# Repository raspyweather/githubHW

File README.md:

#  Github Calendar in Hardware
This is a very basic try to bring github's calendar to hardware. Who wouldn't like to get up and look at the glorious contribution history of the path?

(not my calendar btw ☺)

# introduction
Since I'm a student, manufacturing cost need to be low, why I decided to use three 10cm x 10cm pcbs and solder all components by hand. Because it is cheaper using one mutli-purpose board than two specific pcb designs, I decided to do so, not assemblying unnecessary components on these boards. 

## first/main pcb
All parts assembled 
- WeMos D1 mini (KiCad files used from https://github.com/jerome-labidurie/d1_mini_kicad)
- 2x [TPIC6B595N](http://www.ti.com/lit/ds/symlink/tpic6b595.pdf)
- [TLC5940](http://www.ti.com/lit/ds/symlink/tlc5940.pdf)
- *some* leds
- 4x Buttons
- 1x Poti

## following two pcbs
- TLC5940
- *some* leds

## Total Circuit (connected ones)
only TLC5940 and leds assembled.

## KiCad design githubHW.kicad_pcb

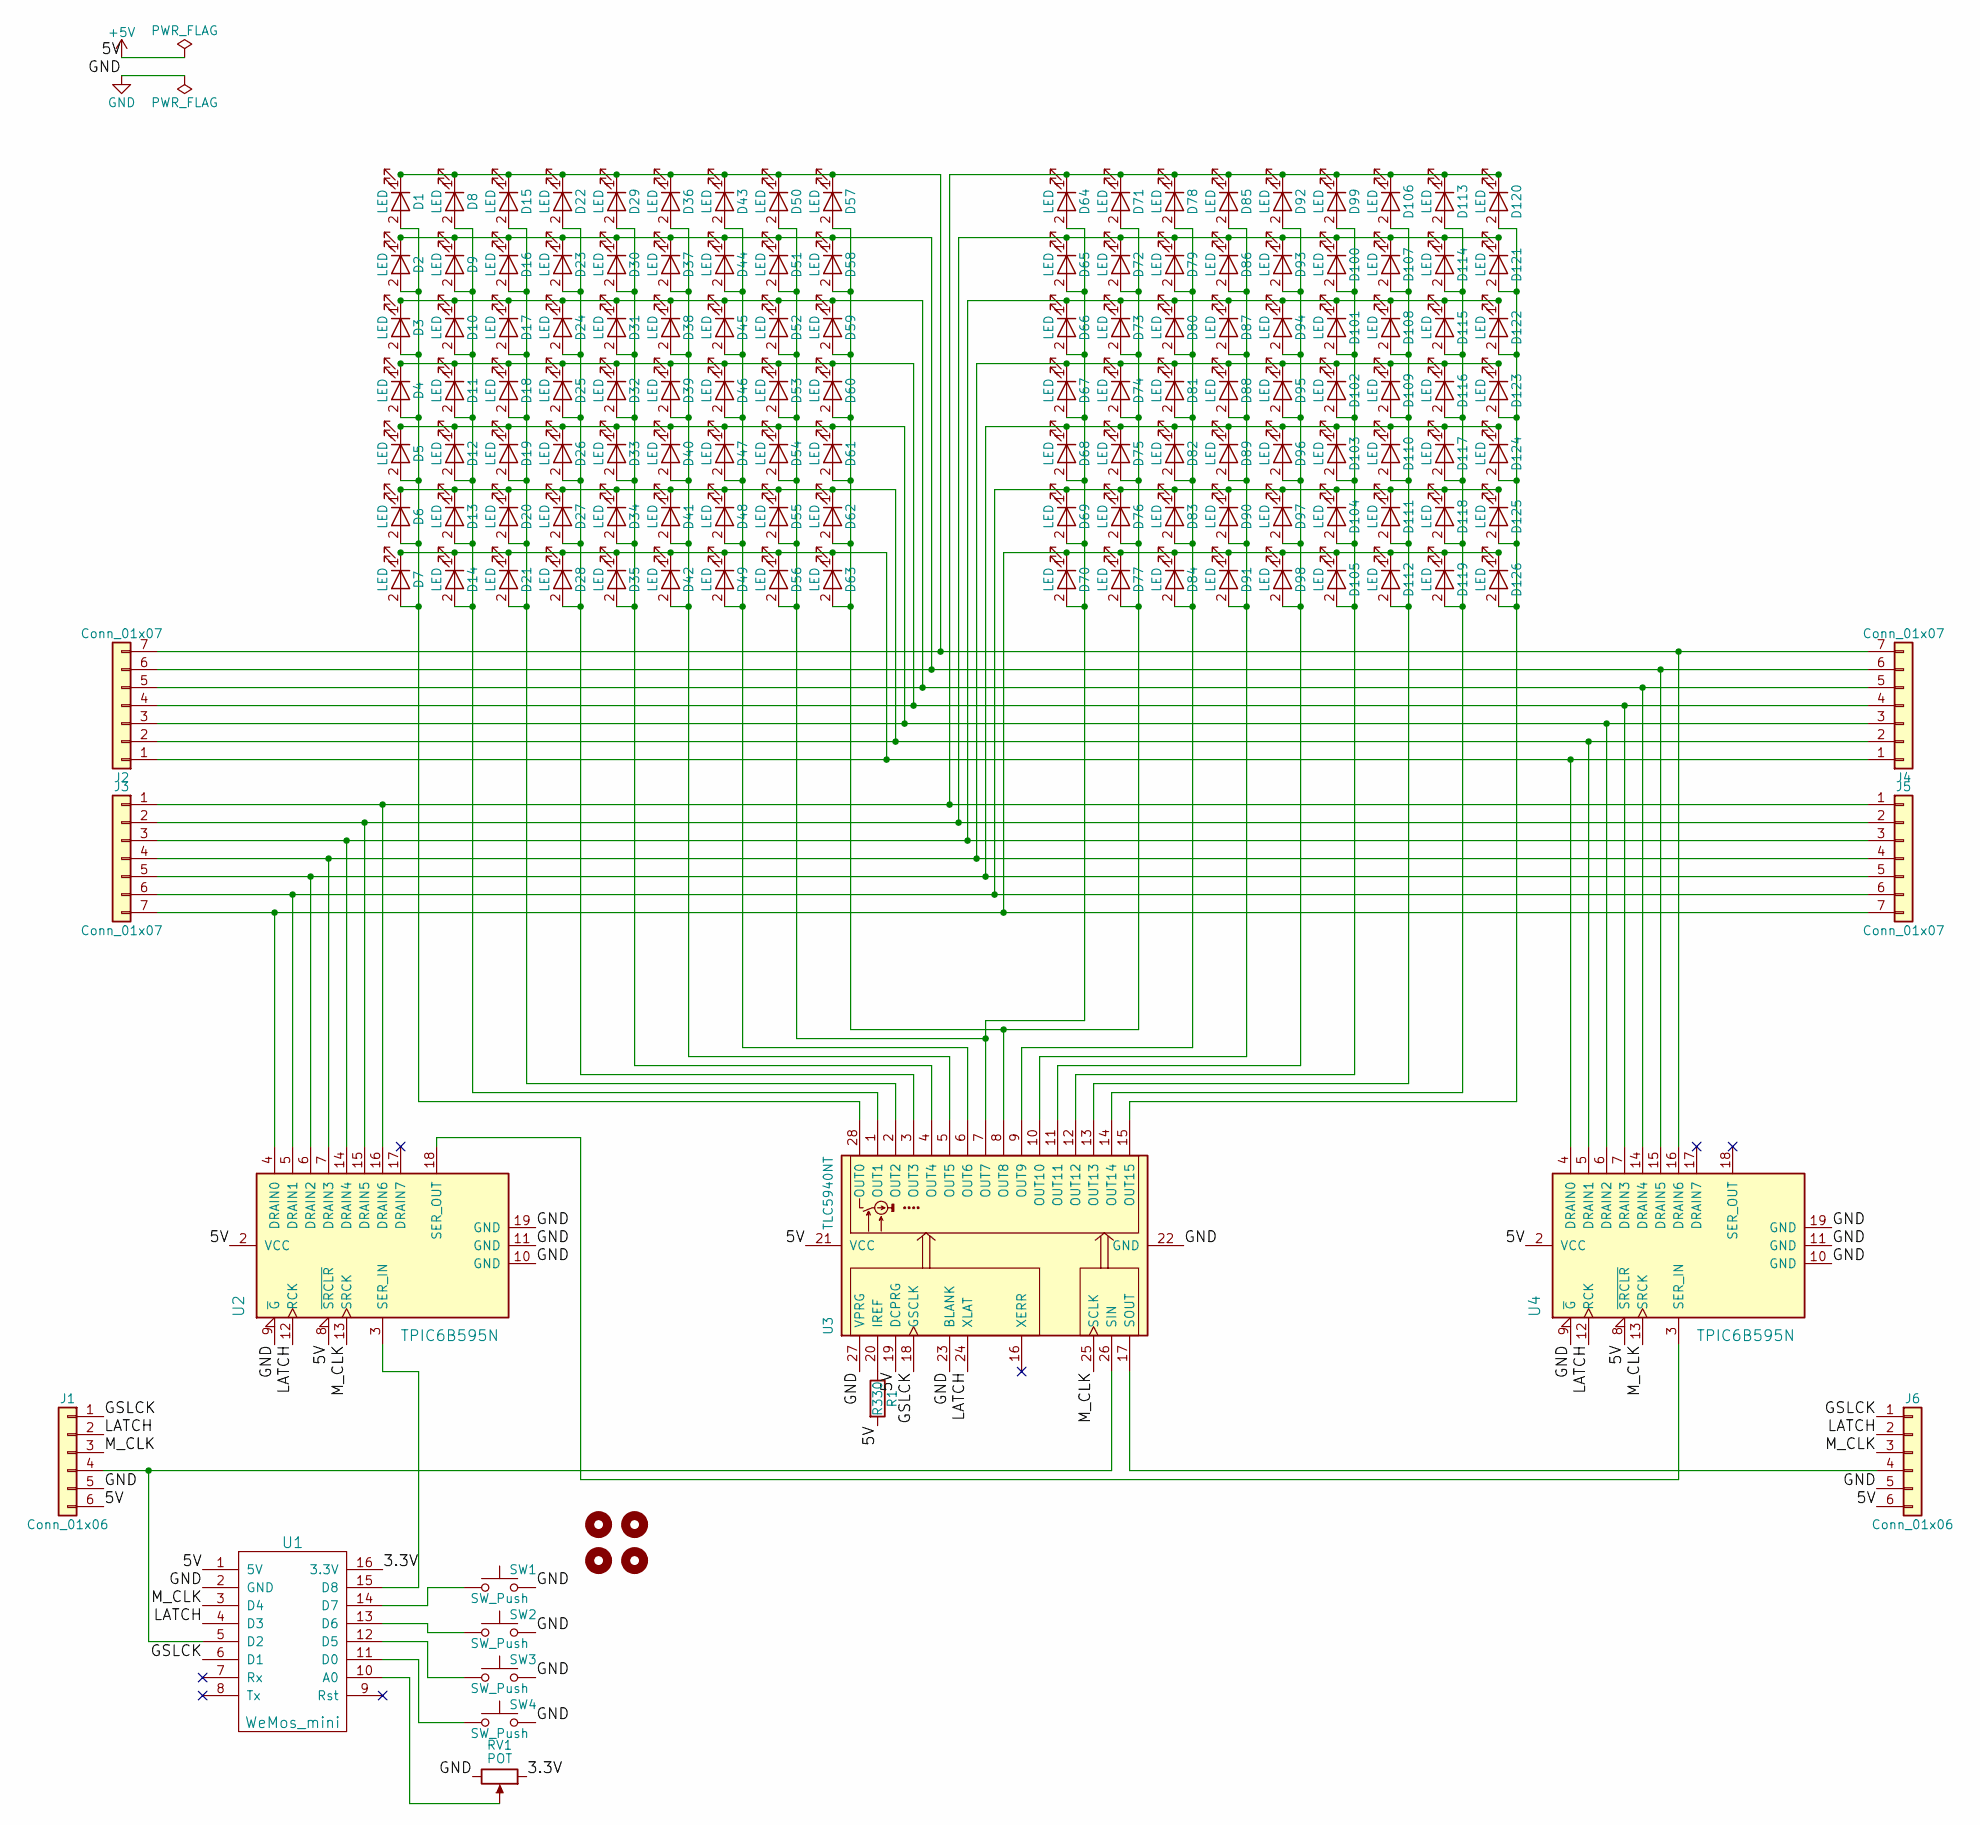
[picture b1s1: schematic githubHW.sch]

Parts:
D1, D2, D3, D4, D5, D6, D7, D8, D9, D10, D11, D12, D13, D14, D15, D16, D17, D18, D19, D20, D21, D22, D23, D24, D25, D26, D27, D28, D29, D30, D31, D32, D33, D34, D35, D36, D37, D38, D39, D40, D41, D42, D43, D44, D45, D46, D47, D48, D49, D50, D51, D52, D53, D54, D55, D56, D57, D58, D59, D60, D61, D62, D63, D64, D65, D66, D67, D68, D69, D70, D71, D72, D73, D74, D75, D76, D77, D78, D79, D80, D81, D82, D83, D84, D85, D86, D87, D88, D89, D90, D91, D92, D93, D94, D95, D96, D97, D98, D99, D100, D101, D102, D103, D104, D105, D106, D107, D108, D109, D110, D111, D112, D113, D114, D115, D116, D117, D118, D119, D120, D121, D122, D123, D124, D125, D126: LED; LED_D3.0mm
J1, J6: Conn_01x06; Pin_Header_Straight_1x06_Pitch2.00mm
J2, J3, J4, J5: Conn_01x07; Pin_Header_Straight_1x07_Pitch2.00mm
MH1, MH2, MH3, MH4: MOUNTHOLE; MountingHole_3.2mm_M3_ISO14580_Pad
R1: R330; R_Axial_DIN0204_L3.6mm_D1.6mm_P7.62mm_Horizontal
RV1: POT; Potentiometer_WirePads_largePads
SW1, SW2, SW3, SW4: SW_Push; SW_PUSH_6mm
U1: WeMos_mini; D1_mini_board
U2, U4: TPIC6B595N; DIP-20_W7.62mm
U3: TLC5940NT; DIP-28_W7.62mm

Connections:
+5V: J1.6, J6.6, R1.2, U1.1 (5V), U2.2 (VCC), U2.8 (~SRCLR), U3.19 (DCPRG), U3.21 (VCC), U4.2 (VCC), U4.8 (~SRCLR)
/3.3V: RV1.1, U1.16 (3.3V)
/GSLCK: J1.1, J6.1, U1.6 (D1), U3.18 (GSCLK)
/LATCH: J1.2, J6.2, U1.4 (D3), U2.12 (RCK), U3.24 (XLAT), U4.12 (RCK)
/M_CLK: J1.3, J6.3, U1.3 (D4), U2.13 (SRCK), U3.25 (SCLK), U4.13 (SRCK)
GND: J1.5, J6.5, RV1.3, SW1.2, SW2.2, SW3.2, SW4.2, U1.2 (GND), U2.9 (~G), U2.10 (GND), U2.11 (GND), U2.19 (GND), U3.22 (GND), U3.23 (BLANK), U3.27 (VPRG), U4.9 (~G), U4.10 (GND), U4.11 (GND), U4.19 (GND)
unnamed: D1.1 (K), D8.1 (K), D15.1 (K), D22.1 (K), D29.1 (K), D36.1 (K), D43.1 (K), D50.1 (K), D57.1 (K), J2.7, J4.7, U4.16 (DRAIN6)
unnamed: D1.2 (A), D2.2 (A), D3.2 (A), D4.2 (A), D5.2 (A), D6.2 (A), D7.2 (A), U3.28 (OUT0)
unnamed: D3.1 (K), D10.1 (K), D17.1 (K), D24.1 (K), D31.1 (K), D38.1 (K), D45.1 (K), D52.1 (K), D59.1 (K), J2.5, J4.5, U4.14 (DRAIN4)
unnamed: D8.2 (A), D9.2 (A), D10.2 (A), D11.2 (A), D12.2 (A), D13.2 (A), D14.2 (A), U3.1 (OUT1)
unnamed: D4.1 (K), D11.1 (K), D18.1 (K), D25.1 (K), D32.1 (K), D39.1 (K), D46.1 (K), D53.1 (K), D60.1 (K), J2.4, J4.4, U4.7 (DRAIN3)
unnamed: D5.1 (K), D12.1 (K), D19.1 (K), D26.1 (K), D33.1 (K), D40.1 (K), D47.1 (K), D54.1 (K), D61.1 (K), J2.3, J4.3, U4.6 (DRAIN2)
unnamed: D6.1 (K), D13.1 (K), D20.1 (K), D27.1 (K), D34.1 (K), D41.1 (K), D48.1 (K), D55.1 (K), D62.1 (K), J2.2, J4.2, U4.5 (DRAIN1)
unnamed: D7.1 (K), D14.1 (K), D21.1 (K), D28.1 (K), D35.1 (K), D42.1 (K), D49.1 (K), D56.1 (K), D63.1 (K), J2.1, J4.1, U4.4 (DRAIN0)
unnamed: D15.2 (A), D16.2 (A), D17.2 (A), D18.2 (A), D19.2 (A), D20.2 (A), D21.2 (A), U3.2 (OUT2)
unnamed: D2.1 (K), D9.1 (K), D16.1 (K), D23.1 (K), D30.1 (K), D37.1 (K), D44.1 (K), D51.1 (K), D58.1 (K), J2.6, J4.6, U4.15 (DRAIN5)
unnamed: D22.2 (A), D23.2 (A), D24.2 (A), D25.2 (A), D26.2 (A), D27.2 (A), D28.2 (A), U3.3 (OUT3)
unnamed: D29.2 (A), D30.2 (A), D31.2 (A), D32.2 (A), D33.2 (A), D34.2 (A), D35.2 (A), U3.4 (OUT4)
unnamed: D36.2 (A), D37.2 (A), D38.2 (A), D39.2 (A), D40.2 (A), D41.2 (A), D42.2 (A), U3.5 (OUT5)
unnamed: D43.2 (A), D44.2 (A), D45.2 (A), D46.2 (A), D47.2 (A), D48.2 (A), D49.2 (A), U3.6 (OUT6)
unnamed: D50.2 (A), D51.2 (A), D52.2 (A), D53.2 (A), D54.2 (A), D55.2 (A), D56.2 (A), D64.2 (A), D65.2 (A), D66.2 (A), D67.2 (A), D68.2 (A), D69.2 (A), D70.2 (A), U3.7 (OUT7)
unnamed: D57.2 (A), D58.2 (A), D59.2 (A), D60.2 (A), D61.2 (A), D62.2 (A), D63.2 (A), D71.2 (A), D72.2 (A), D73.2 (A), D74.2 (A), D75.2 (A), D76.2 (A), D77.2 (A), U3.8 (OUT8)
unnamed: D78.2 (A), D79.2 (A), D80.2 (A), D81.2 (A), D82.2 (A), D83.2 (A), D84.2 (A), U3.9 (OUT9)
unnamed: D85.2 (A), D86.2 (A), D87.2 (A), D88.2 (A), D89.2 (A), D90.2 (A), D91.2 (A), U3.10 (OUT10)
unnamed: D92.2 (A), D93.2 (A), D94.2 (A), D95.2 (A), D96.2 (A), D97.2 (A), D98.2 (A), U3.11 (OUT11)
unnamed: D65.1 (K), D72.1 (K), D79.1 (K), D86.1 (K), D93.1 (K), D100.1 (K), D107.1 (K), D114.1 (K), D121.1 (K), J3.2, J5.2, U2.15 (DRAIN5)
unnamed: D99.2 (A), D100.2 (A), D101.2 (A), D102.2 (A), D103.2 (A), D104.2 (A), D105.2 (A), U3.12 (OUT12)
unnamed: D66.1 (K), D73.1 (K), D80.1 (K), D87.1 (K), D94.1 (K), D101.1 (K), D108.1 (K), D115.1 (K), D122.1 (K), J3.3, J5.3, U2.14 (DRAIN4)
unnamed: D67.1 (K), D74.1 (K), D81.1 (K), D88.1 (K), D95.1 (K), D102.1 (K), D109.1 (K), D116.1 (K), D123.1 (K), J3.4, J5.4, U2.7 (DRAIN3)
unnamed: D68.1 (K), D75.1 (K), D82.1 (K), D89.1 (K), D96.1 (K), D103.1 (K), D110.1 (K), D117.1 (K), D124.1 (K), J3.5, J5.5, U2.6 (DRAIN2)
unnamed: D69.1 (K), D76.1 (K), D83.1 (K), D90.1 (K), D97.1 (K), D104.1 (K), D111.1 (K), D118.1 (K), D125.1 (K), J3.6, J5.6, U2.5 (DRAIN1)
unnamed: D70.1 (K), D77.1 (K), D84.1 (K), D91.1 (K), D98.1 (K), D105.1 (K), D112.1 (K), D119.1 (K), D126.1 (K), J3.7, J5.7, U2.4 (DRAIN0)
unnamed: D64.1 (K), D71.1 (K), D78.1 (K), D85.1 (K), D92.1 (K), D99.1 (K), D106.1 (K), D113.1 (K), D120.1 (K), J3.1, J5.1, U2.16 (DRAIN6)
unnamed: D106.2 (A), D107.2 (A), D108.2 (A), D109.2 (A), D110.2 (A), D111.2 (A), D112.2 (A), U3.13 (OUT13)
unnamed: D113.2 (A), D114.2 (A), D115.2 (A), D116.2 (A), D117.2 (A), D118.2 (A), D119.2 (A), U3.14 (OUT14)
unnamed: D120.2 (A), D121.2 (A), D122.2 (A), D123.2 (A), D124.2 (A), D125.2 (A), D126.2 (A), U3.15 (OUT15)
unnamed: J1.4, U1.5 (D2), U3.26 (SIN)
unnamed: J6.4, U3.17 (SOUT)
unnamed: R1.1, U3.20 (IREF)
unnamed: RV1.2, U1.10 (A0)
unnamed: SW1.1, U1.14 (D7)
unnamed: SW2.1, U1.13 (D6)
unnamed: SW3.1, U1.12 (D5)
unnamed: SW4.1, U1.11 (D0)
unnamed: U1.15 (D8), U2.3 (SER_IN)
unnamed: U2.18 (SER_OUT), U4.3 (SER_IN)

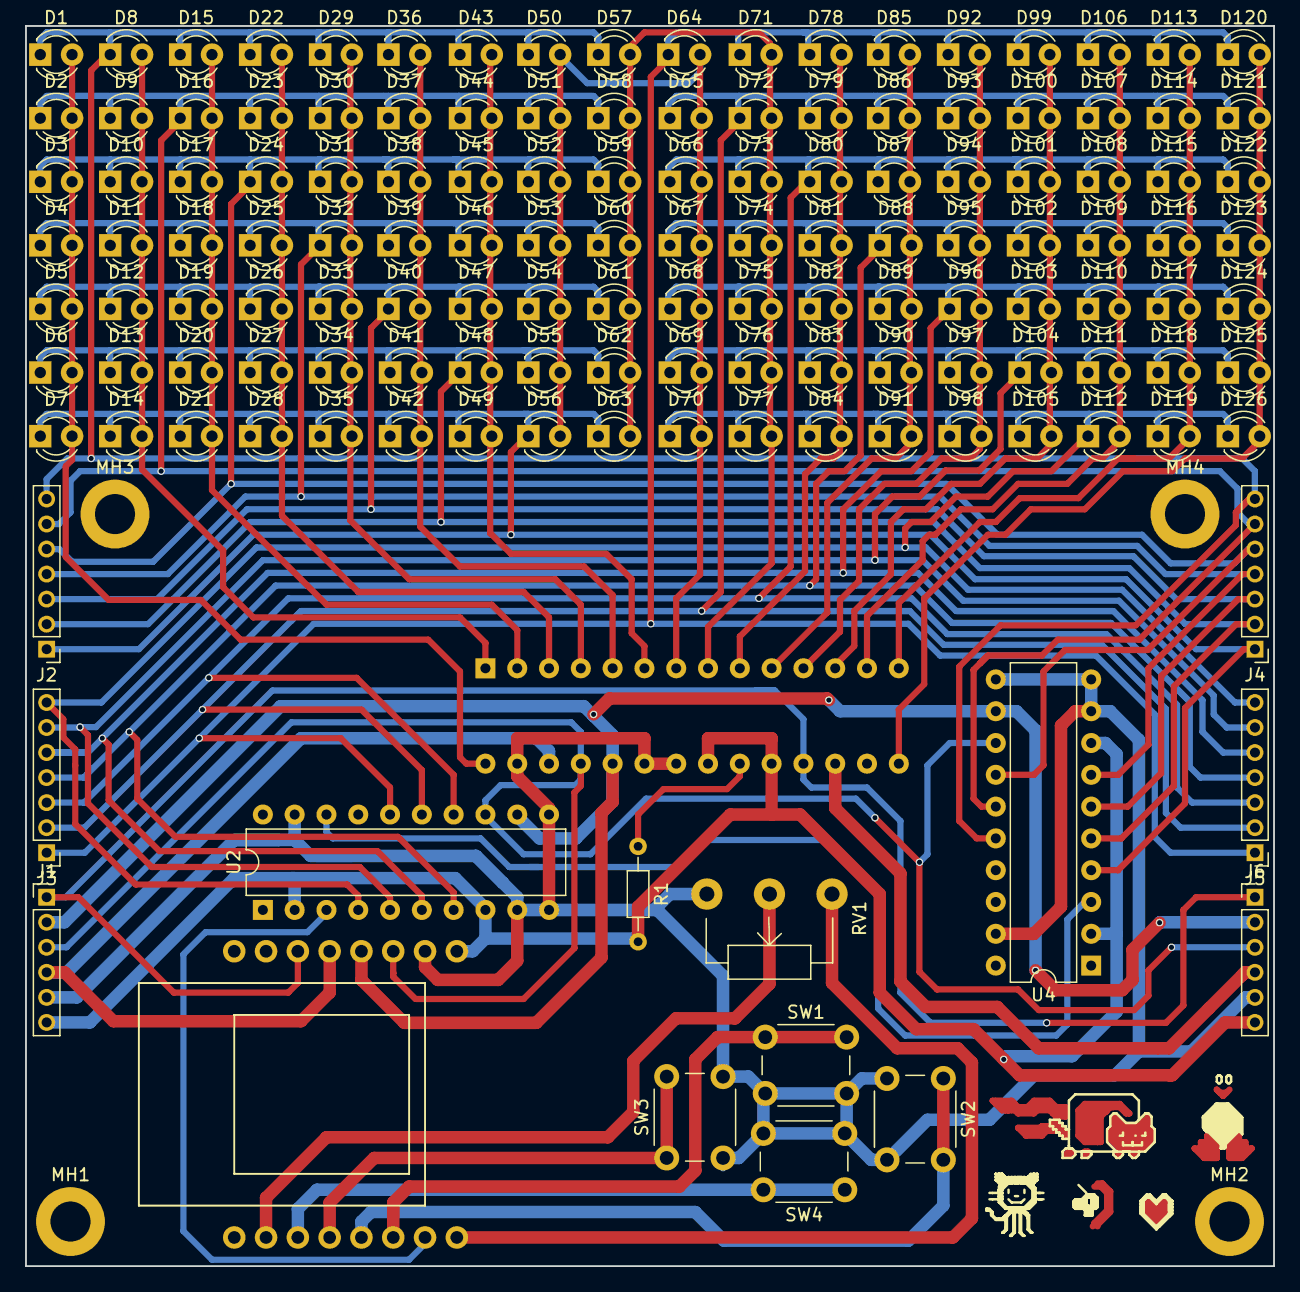
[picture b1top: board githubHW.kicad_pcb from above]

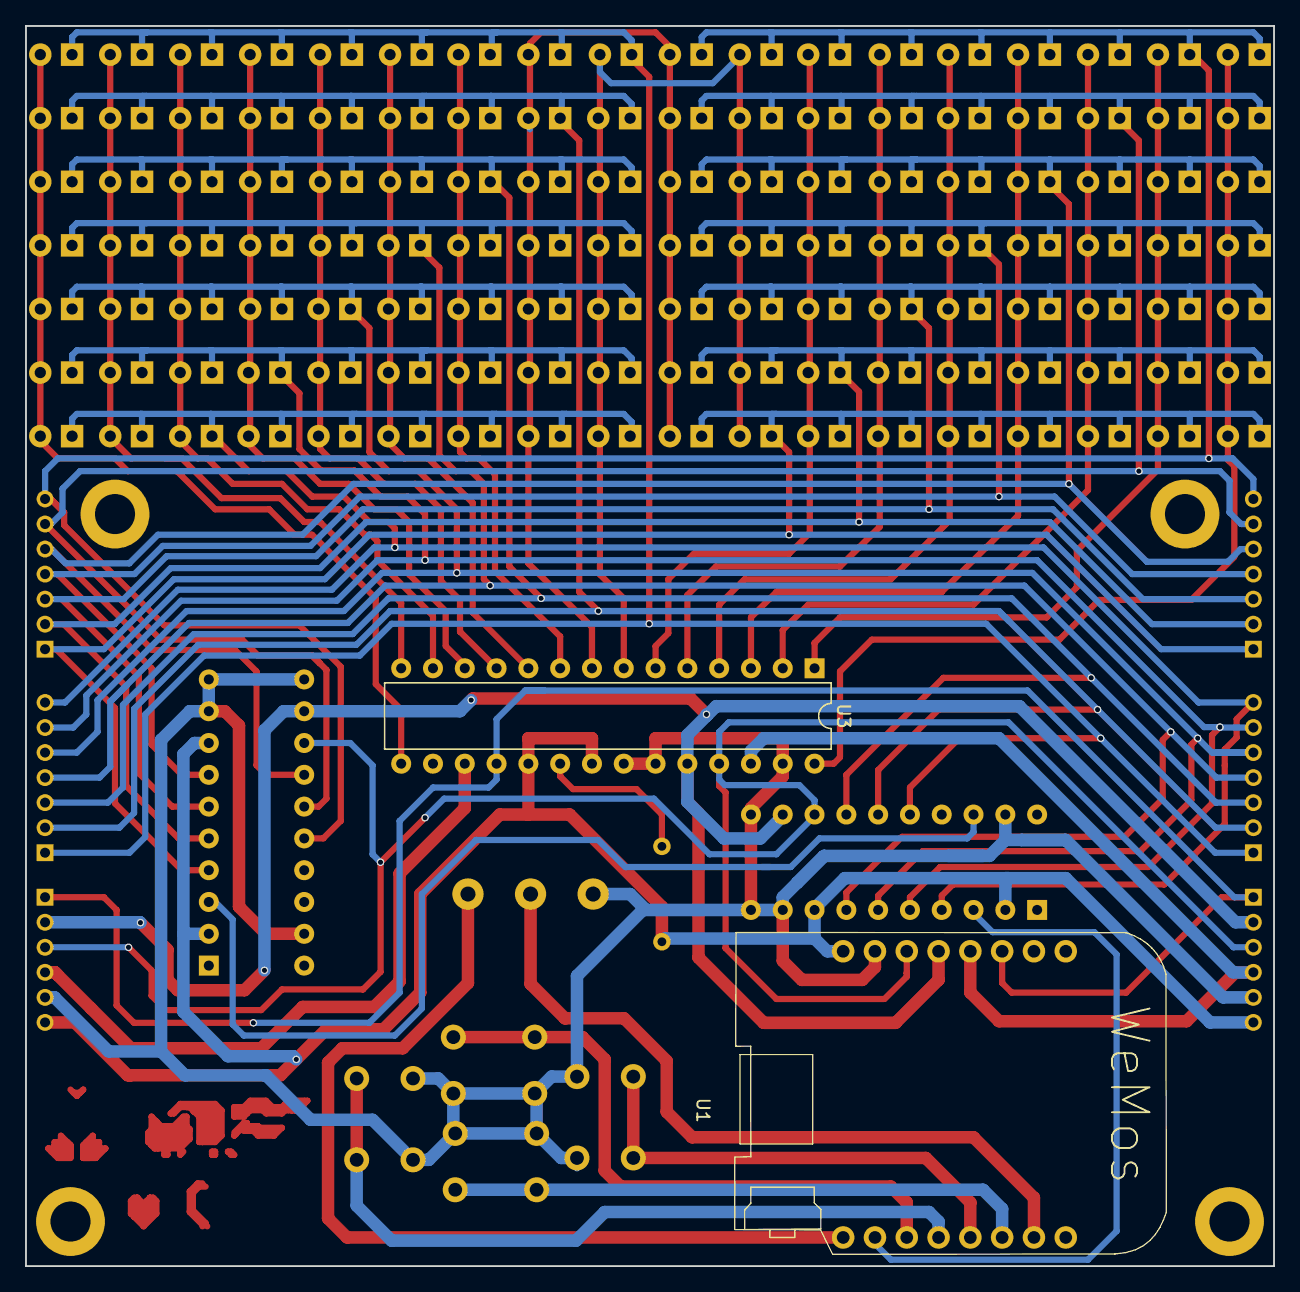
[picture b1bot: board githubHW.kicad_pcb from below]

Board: 2 copper layers, 99.7 x 99.1 mm, 146 parts (2 on the bottom side), 46 nets.

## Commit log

2017-12-30 files added to vcs
2017-12-30 plotted pcb view added
2018-01-01 connection issue fixed
2018-01-01 board svg updated
2018-01-01 buttons connection changed
    now using WeMos' pullups
2018-01-07 Revert "connection issue fixed"
    This reverts commit d7eb6beb1c8d570a5e8c06e88c024579e6cb722b.
2018-01-07 documentation added
2018-01-07 documentation fix
2018-01-07 submodule removed and readded as folder
2018-01-07 documentation updated
2018-01-07 documentation reworked
2018-01-09 poti connection corrected
2018-01-16 wemos files commited for better usability.
2018-01-17 scheme simplified for easier control
2018-01-18 tux added ♥
2018-01-20 removed backup file
2018-01-20 gerber files added
